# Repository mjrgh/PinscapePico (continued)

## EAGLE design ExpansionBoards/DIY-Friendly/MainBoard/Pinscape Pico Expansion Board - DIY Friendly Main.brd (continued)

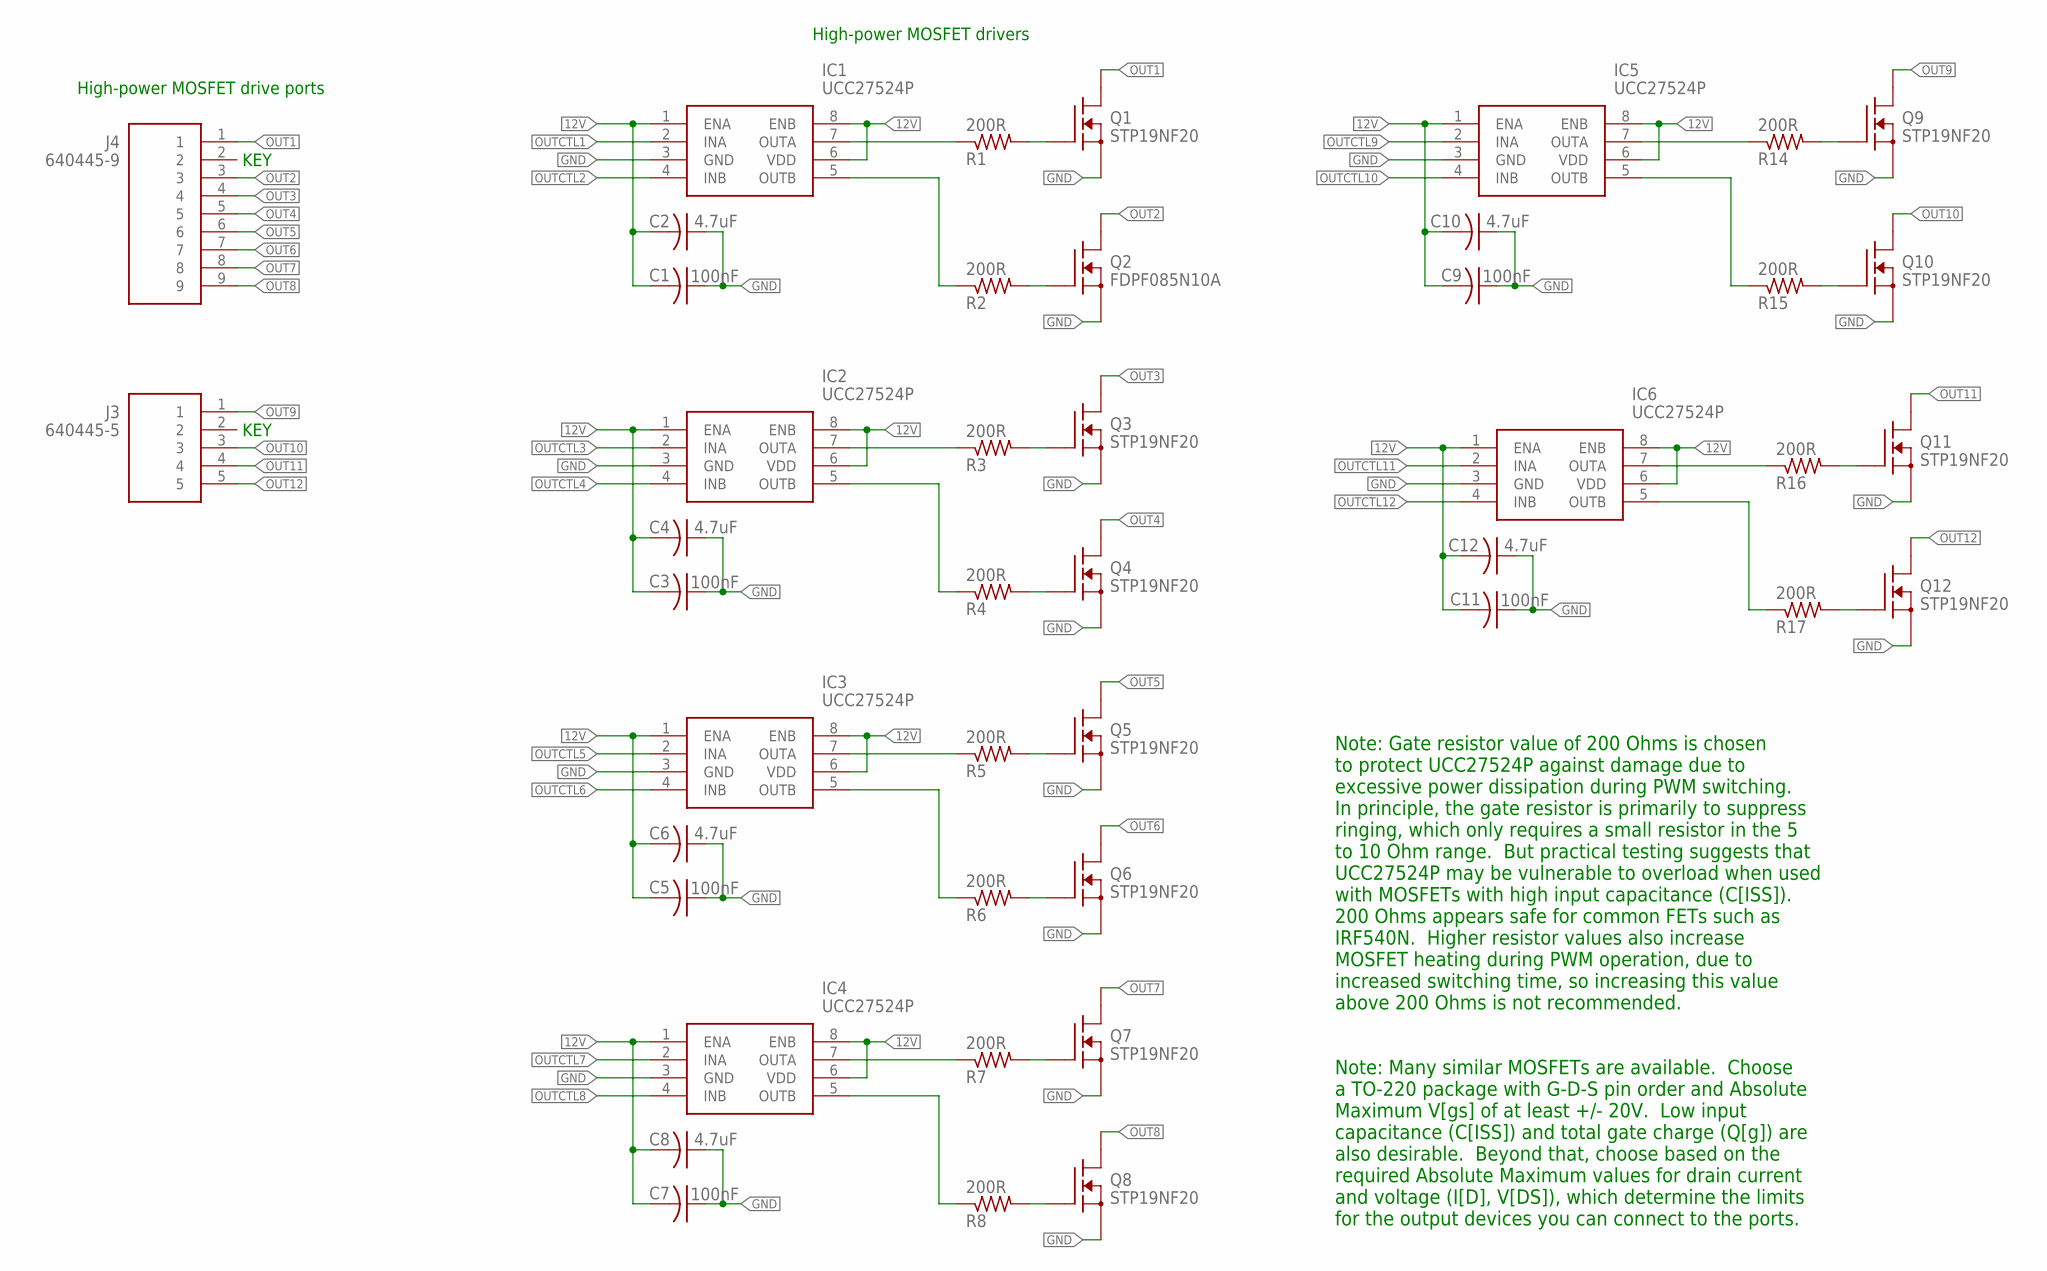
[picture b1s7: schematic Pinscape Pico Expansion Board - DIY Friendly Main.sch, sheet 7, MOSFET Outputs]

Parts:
C1, C3, C5, C7, C9, C11: 100nF; C025-024X044; PARTNO K104K15X7RF5TL2
C2, C4, C6, C8, C10, C12: 4.7uF; C025-024X044; PARTNO 810-FG14X5R1H475KRT0
IC1, IC2, IC3, IC4, IC5, IC6: UCC27524P; DIP794W53P254L959H508Q8N
J3: 640445-5; HDRV5W117P0X396_1X5_1981X762X1
J4: 640445-9; SHDR9W117P0X396_1X9_3566X762X1
Q1, Q3, Q4, Q5, Q6, Q7, Q8, Q9, Q10, Q11, Q12: STP19NF20; TO220BV; PARTNO FDPF085N10A
Q2: FDPF085N10A; TO220BV; PARTNO FDPF085N10A
R1, R2, R3, R4, R5, R6, R7, R8, R14, R15, R16, R17: 200R; 0204/5; PARTNO 660-MFS1/4DCT52R47R0

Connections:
12V: C1.2, C2.2, C3.2, C4.2, C5.2, C6.2, C7.2, C8.2, C9.2, C10.2, C11.2, C12.2, IC1.1 (ENA), IC1.6 (VDD), IC1.8 (ENB), IC2.1 (ENA), IC2.6 (VDD), IC2.8 (ENB), IC3.1 (ENA), IC3.6 (VDD), IC3.8 (ENB), IC4.1 (ENA), IC4.6 (VDD), IC4.8 (ENB), IC5.1 (ENA), IC5.6 (VDD), IC5.8 (ENB), IC6.1 (ENA), IC6.6 (VDD), IC6.8 (ENB); also elsewhere on the board
GND: C1.1, C2.1, C3.1, C4.1, C5.1, C6.1, C7.1, C8.1, C9.1, C10.1, C11.1, C12.1, IC1.3 (GND), IC2.3 (GND), IC3.3 (GND), IC4.3 (GND), IC5.3 (GND), IC6.3 (GND), Q1.3 (S), Q2.3 (S), Q3.3 (S), Q4.3 (S), Q5.3 (S), Q6.3 (S), Q7.3 (S), Q8.3 (S), Q9.3 (S), Q10.3 (S), Q11.3 (S), Q12.3 (S); also elsewhere on the board
unnamed: IC1.7 (OUTA), R1.1
unnamed: IC1.5 (OUTB), R2.1
unnamed: Q1.1 (G), R1.2
unnamed: Q2.1 (G), R2.2
unnamed: IC2.7 (OUTA), R3.1
unnamed: IC2.5 (OUTB), R4.1
unnamed: Q3.1 (G), R3.2
unnamed: Q4.1 (G), R4.2
unnamed: IC3.7 (OUTA), R5.1
unnamed: IC3.5 (OUTB), R6.1
unnamed: Q5.1 (G), R5.2
unnamed: Q6.1 (G), R6.2
unnamed: IC4.7 (OUTA), R7.1
unnamed: IC4.5 (OUTB), R8.1
unnamed: Q7.1 (G), R7.2
unnamed: Q8.1 (G), R8.2
unnamed: IC5.7 (OUTA), R14.1
unnamed: IC5.5 (OUTB), R15.1
unnamed: Q9.1 (G), R14.2
unnamed: Q10.1 (G), R15.2
unnamed: IC6.7 (OUTA), R16.1
unnamed: IC6.5 (OUTB), R17.1
unnamed: Q11.1 (G), R16.2
unnamed: Q12.1 (G), R17.2
OUT1: J4.1, Q1.2 (D)
OUT2: J4.3, Q2.2 (D)
OUT3: J4.4, Q3.2 (D)
OUT4: J4.5, Q4.2 (D)
OUT5: J4.6, Q5.2 (D)
OUT6: J4.7, Q6.2 (D)
OUT7: J4.8, Q7.2 (D)
OUT8: J4.9, Q8.2 (D)
OUT9: J3.1, Q9.2 (D)
OUT10: J3.3, Q10.2 (D)
OUT11: J3.4, Q11.2 (D)
OUT12: J3.5, Q12.2 (D)
OUTCTL1: IC1.2 (INA); also elsewhere on the board
OUTCTL2: IC1.4 (INB); also elsewhere on the board
OUTCTL3: IC2.2 (INA); also elsewhere on the board
OUTCTL4: IC2.4 (INB); also elsewhere on the board
OUTCTL5: IC3.2 (INA); also elsewhere on the board
OUTCTL6: IC3.4 (INB); also elsewhere on the board
OUTCTL7: IC4.2 (INA); also elsewhere on the board
OUTCTL8: IC4.4 (INB); also elsewhere on the board
OUTCTL9: IC5.2 (INA); also elsewhere on the board
OUTCTL10: IC5.4 (INB); also elsewhere on the board
OUTCTL11: IC6.2 (INA); also elsewhere on the board
OUTCTL12: IC6.4 (INB); also elsewhere on the board

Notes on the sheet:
High-power MOSFET drive ports
KEY
High-power MOSFET drivers
Note: Gate resistor value of 200 Ohms is chosen to protect UCC27524P against damage due to excessive power dissipation during PWM switching. In principle, the gate resistor is primarily to suppress ringing, which only requires a small resistor in the 5 to 10 Ohm range. But practical testing suggest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
Note: Many similar MOSFETs are available. Choose a TO-220 package with G-D-S pin order and Absolute Maximum V[gs] of at least +/- 20V. Low input capacitance (C[ISS]) and total gate charge (Q[g]) are also desirable. Beyond that, choose based on the required Absolute Maximum values for drain current 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

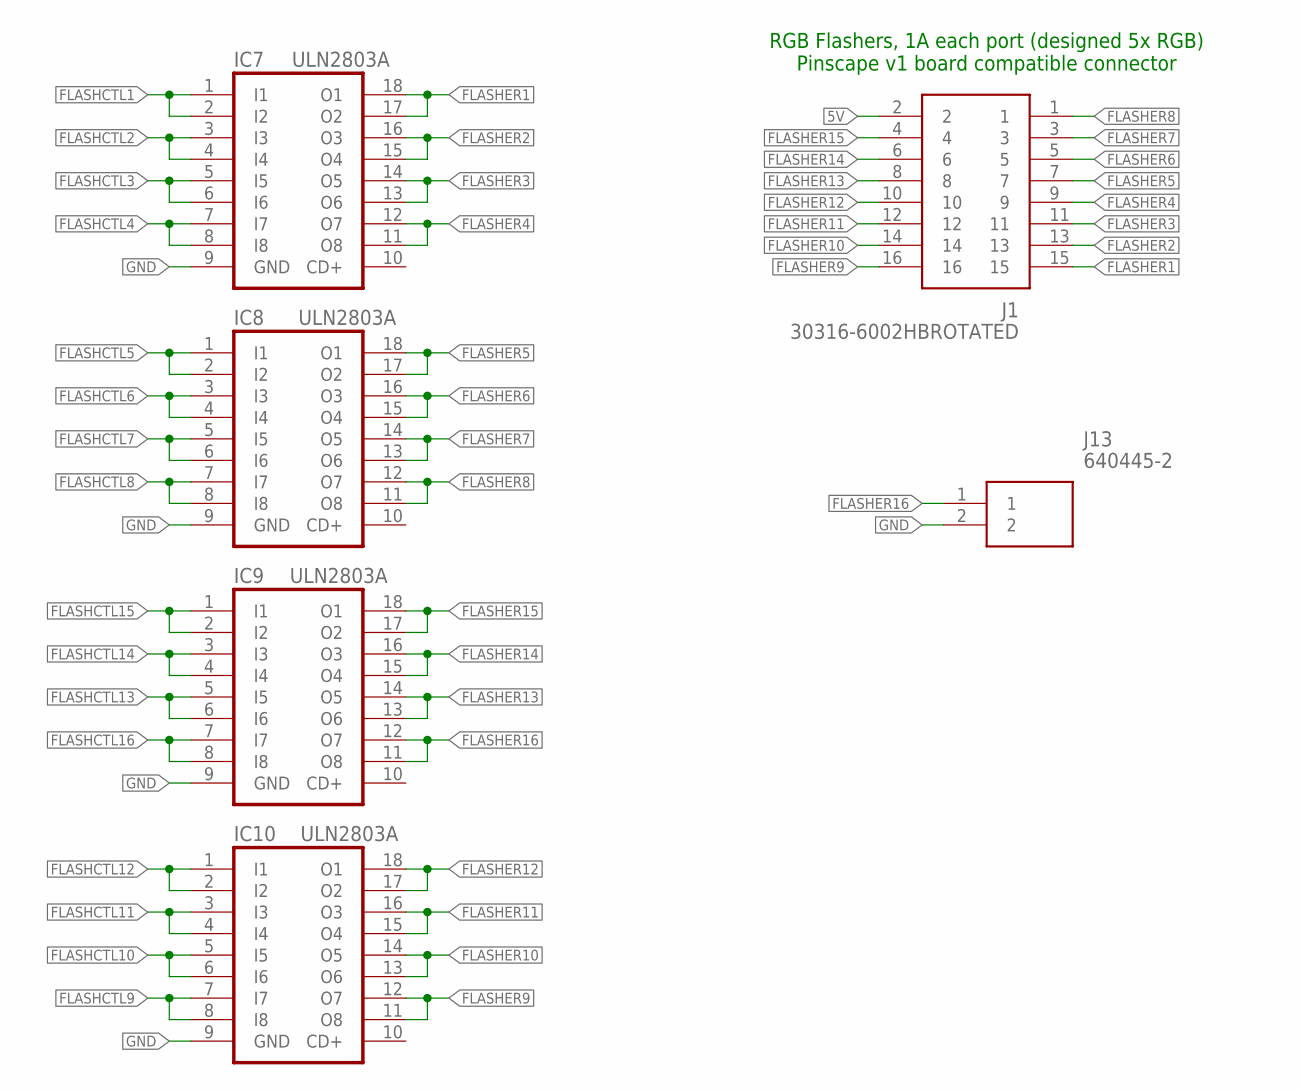
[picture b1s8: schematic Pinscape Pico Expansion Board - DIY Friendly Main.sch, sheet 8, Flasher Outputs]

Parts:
IC7, IC8, IC9, IC10: ULN2803A; DIL18
J1: 30316-6002HBROTATED; 3M-30316-6002HB-ROTATED
J13: 640445-2; SHDR2W117P0X396_1X2_792X762X11

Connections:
5V: J1.2; also elsewhere on the board
FLASHCTL1: IC7.1 (I1), IC7.2 (I2); also elsewhere on the board
FLASHCTL2: IC7.3 (I3), IC7.4 (I4); also elsewhere on the board
FLASHCTL3: IC7.5 (I5), IC7.6 (I6); also elsewhere on the board
FLASHCTL4: IC7.7 (I7), IC7.8 (I8); also elsewhere on the board
FLASHCTL5: IC8.1 (I1), IC8.2 (I2); also elsewhere on the board
FLASHCTL6: IC8.3 (I3), IC8.4 (I4); also elsewhere on the board
FLASHCTL7: IC8.5 (I5), IC8.6 (I6); also elsewhere on the board
FLASHCTL8: IC8.7 (I7), IC8.8 (I8); also elsewhere on the board
FLASHCTL9: IC10.7 (I7), IC10.8 (I8); also elsewhere on the board
FLASHCTL10: IC10.5 (I5), IC10.6 (I6); also elsewhere on the board
FLASHCTL11: IC10.3 (I3), IC10.4 (I4); also elsewhere on the board
FLASHCTL12: IC10.1 (I1), IC10.2 (I2); also elsewhere on the board
FLASHCTL13: IC9.5 (I5), IC9.6 (I6); also elsewhere on the board
FLASHCTL14: IC9.3 (I3), IC9.4 (I4); also elsewhere on the board
FLASHCTL15: IC9.1 (I1), IC9.2 (I2); also elsewhere on the board
FLASHCTL16: IC9.7 (I7), IC9.8 (I8); also elsewhere on the board
FLASHER1: IC7.17 (O2), IC7.18 (O1), J1.15
FLASHER2: IC7.15 (O4), IC7.16 (O3), J1.13
FLASHER3: IC7.13 (O6), IC7.14 (O5), J1.11
FLASHER4: IC7.11 (O8), IC7.12 (O7), J1.9
FLASHER5: IC8.17 (O2), IC8.18 (O1), J1.7
FLASHER6: IC8.15 (O4), IC8.16 (O3), J1.5
FLASHER7: IC8.13 (O6), IC8.14 (O5), J1.3
FLASHER8: IC8.11 (O8), IC8.12 (O7), J1.1
FLASHER9: IC10.11 (O8), IC10.12 (O7), J1.16
FLASHER10: IC10.13 (O6), IC10.14 (O5), J1.14
FLASHER11: IC10.15 (O4), IC10.16 (O3), J1.12
FLASHER12: IC10.17 (O2), IC10.18 (O1), J1.10
FLASHER13: IC9.13 (O6), IC9.14 (O5), J1.8
FLASHER14: IC9.15 (O4), IC9.16 (O3), J1.6
FLASHER15: IC9.17 (O2), IC9.18 (O1), J1.4
FLASHER16: IC9.11 (O8), IC9.12 (O7), J13.1
GND: IC7.9 (GND), IC8.9 (GND), IC9.9 (GND), IC10.9 (GND), J13.2; also elsewhere on the board

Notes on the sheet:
RGB Flashers, 1A each port (designed 5x RGB) Pinscape v1 board compatible connector

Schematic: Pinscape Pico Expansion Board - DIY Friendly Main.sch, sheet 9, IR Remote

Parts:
C14: 4.7uF; C025-024X044; PARTNO 810-FG14X5R1H475KRT0
D3, D4: 1N4148; DO35-7
J10: 215079-4; 2150794
J11: 640454-2; HDRV2W66P0X254_1X2_762X572X100
Q13: BC337-25; BC33725
R19: 540R; 0204/7; PARTNO 660-MFS1/4DCT52R47R0
R31: 2R5; 0204/7; PARTNO 660-MFS1/4DCT52R47R0

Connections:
3V3_PICO: J10.1; also elsewhere on the board
5V: C14.1, J11.1; also elsewhere on the board
$N377: D3.A, Q13.2 (B), R19.2
GND: C14.2, D4.C, J10.2, J10.4, R31.1; also elsewhere on the board
IR_IN: J10.3; also elsewhere on the board
IR_LED_CATHODE: J11.2, Q13.1 (C)
IR_OUT: R19.1; also elsewhere on the board
unnamed: D3.C, D4.A
unnamed: Q13.3 (E), R31.2

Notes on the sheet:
IR REMOTE CONTROL TRANSMITTER Use with VSLB4940, TSAL6400, or a similar IR LED with a peak wavelength around 940nm. Set the current-sense resistor according to the desired forward current on the IR LED. Set to 200 mA for VSLB4940 or TSAL6400; for others, use a current between the "continuous" and "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
IR REMOTE RECEIVER CONNECTOR This header allows connecting an IR receiver (TSOP38438) on a separate circuit board, connected to the main board with a 4-conductor ribbon cable. The board should include the VCC supply filter circuit (220R + 150nF) shown in the data sheet.
===> IRED Cathode (-)
===> IRED Anode (+)
Note: TE Connectivity Micro-Match 215079-4 base pairs with 215083-4 on-cable IDC connector.
CURRENT-SENSE RESISTOR Resistor sets current to I(LED) = 0.5V/R R=2.5 ohms -> 200mA current
NPN substitutes: choose any medium-power NPN with Hfe around 100
IR EMITTER / IR RECEIVER The emitter and receiver are designed to be installed remotely to allow placing them in suitable line-of-sight locations.

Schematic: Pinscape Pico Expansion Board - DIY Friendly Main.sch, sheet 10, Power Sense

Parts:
C13: 100nF; C025-024X044; PARTNO K104K15X7RF5TL2
IC11: SN74HC74NE4; DIP794W53P254L1930H508Q14N
IC12: S-80833CLY; TO-92_(TO-226)
IC13: PC827; DIL08
R18: 240R; 0204/7; PARTNO 660-MFS1/4DCT52R47R0
R20, R22: 10K; 0204/7; PARTNO mfr-12frrf52-10k
R21: 360R; 0204/7; PARTNO 660-MFS1/4DCT52R47R0

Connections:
3V3_PICO: IC13.6 (COL); also elsewhere on the board
5V: C13.1, IC11.2 (1D), IC11.4 (1!PRE), IC11.14 (VCC), IC12.2 (VDD), IC13.8 (COL); also elsewhere on the board
GND: C13.2, IC11.7 (GND), IC12.3 (GND), R18.1, R20.2, R21.1, R22.1; also elsewhere on the board
unnamed: IC11.3 (1CLK), IC13.7 (EMIT), R20.1
unnamed: IC13.2 (C), R18.2
unnamed: IC11.1 (!1CLR), IC12.1 (OUT)
unnamed: IC13.4 (C), R21.2
unnamed: IC11.5 (1Q), IC13.3 (A)
PSU2_STATUS_SENSE: IC13.5 (EMIT), R22.2; also elsewhere on the board
PSU2_STATUS_SET: IC13.1 (A); also elsewhere on the board

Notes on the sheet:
PSU2 Power Sensing This circuit monitors the status of a secondary power supply (PSU2) that's hard-switched on and off with the overall pinball cabinet power. The status circuit maintains its own memory of the power state, independently of the Pico's power state, which satisfies two important condi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
POR part selection: The POR is triggered by the voltage on the 5V supply crossing a threshold voltage, so we must choose a POR whose threshold voltage slightly below the MINIMUM voltage that the 5V supply maintains when powered on and operating stably. Nominally, this would be 4.75V for an ATX supp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
Note: RESET signal must be ACTIVE LOW

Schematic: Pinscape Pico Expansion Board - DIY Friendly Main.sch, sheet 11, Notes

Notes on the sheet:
I2C Address Map (7-bit notation) $18 LIS3DH (Accelerometer) $30 Pico PWM Helper (main board) $31 Pico PWM Helper #1 (power board) $32 Pico PWM Helper #2 (power board) $48 ADS1115 (ADC) $68 DS1307 (RTC clock/calendar chip) [On Power board]
Copyright and License Info Pinscape Pico DIY Friendly Expansion Board Copyright 2024, 2025 Michael J Roberts BSD 3-clause license

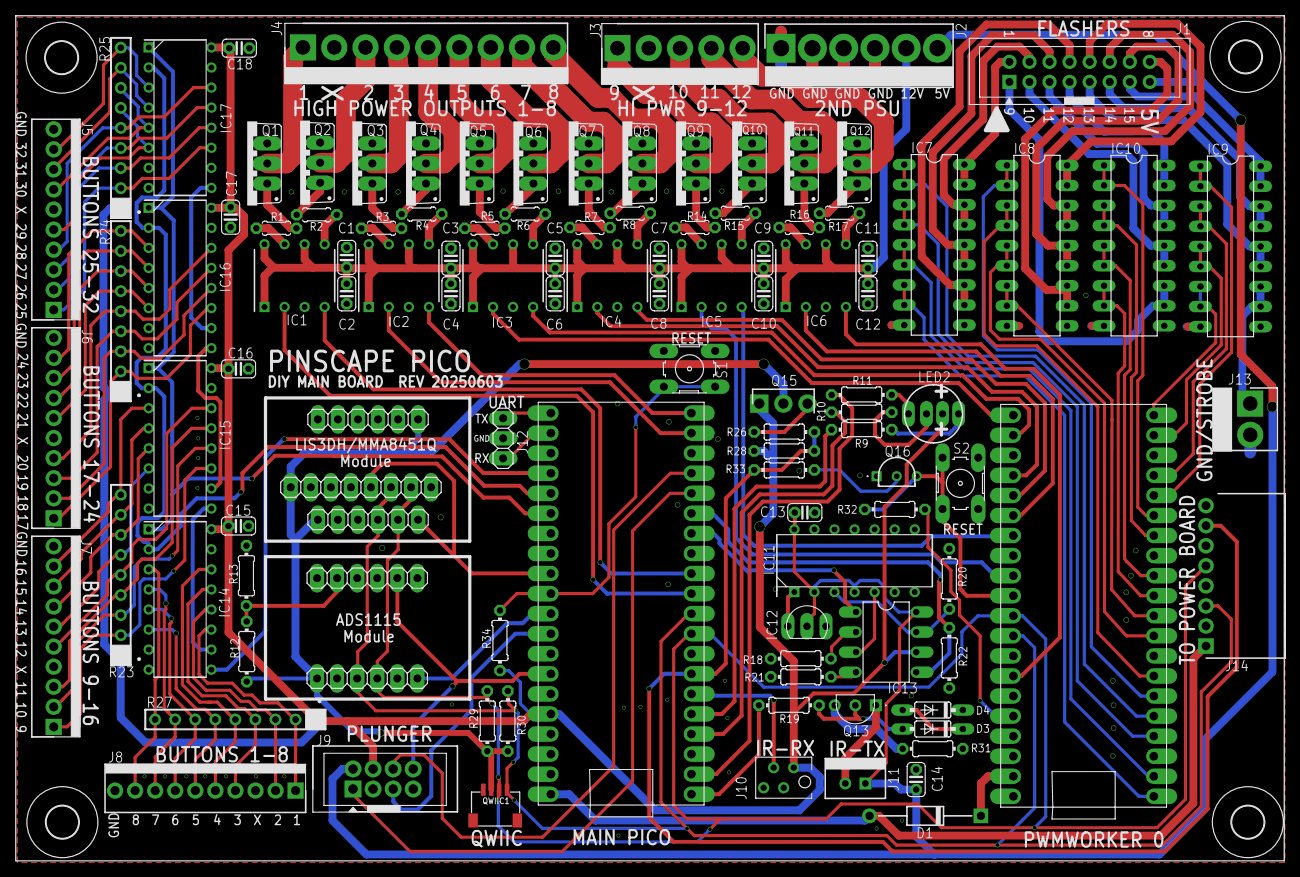
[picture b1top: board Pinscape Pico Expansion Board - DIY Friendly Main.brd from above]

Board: 2 copper layers, 160.6 x 107.0 mm, 116 parts (0 on the bottom side), 161 nets.

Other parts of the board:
U$1, U$2, U$3, U$4: 4,1

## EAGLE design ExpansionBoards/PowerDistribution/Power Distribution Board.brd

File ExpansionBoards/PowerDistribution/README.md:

# Pinscape Pico Power Distribution Board

This is a prototype design for a power distribution board for virtual
pinball cabinets.  It's nominally designed to be used with the
Pinscape Pico expansion boards, but it could really be used with just
about any pin cab setup, with or without an I/O board like Pinscape.

## 120VAC vs 220/230/240VAC

I use the term "120VAC" here to refer to the line voltage - the
voltage from your wall outlet plug.  I call it "120VAC" just to make
it concrete and avoid jargon, but it makes it sound like you can
*only* use the board with 120VAC plugs, which isn't true.  What I
really mean is **line voltage**, whatever that happens to be in your
region.

To be clear, the board will also work in countries with 220VAC to
240VAC outlets, which is the standard in Europe and many other parts
of the world.

The board really doesn't care what the line voltage is, because it
doesn't have any transformers or other parts designed around specific
voltages.  It just routes the line voltage to the various headers.
That lets you use any voltage, as long as it's within the upper limits
for all of the parts.  The limiting factor is the switching relay,
which is rated for up to 240VAC.

## Danger - high voltage

This board provides connections to the 120VAC (or 240VAC) wall outlet
power inputs to the various DC power supplies.  It also has a section
for 48VDC power.  Line voltage and 48VDC are both hazardous, capable
of causing electric shock and fires.  The board must be installed in
the cabinet so that it's shielded from accidental contact with the
operator or contact with loose articles.  It should have either a
grounded metal enclosure (grounded to Earth ground through the AC
outlet) or an insulated enclosure.  Always unplug it from all outside
power sources when doing any work on the board.

## Features

This board has several functions special to pin cabs:

* "Smart" power switching: Virtual pin cabs typically have two or
more DC power supplies: the ATX power supply that runs the main PC,
and one or more auxiliary supplies for running feedback devices
(lights, motors, solenoids, etc).  There are often several auxiliary
supplies to meet the varying voltage requirements for the feedback
devices, such as a 24V supply for contactors and solenoids, a 48V
supply for pinball coils, and a 5V/12V dual supply for LEDs, motors,
and smaller solenoids.  Most people like to use a single "soft power"
button to control power to the PC, and would like all of the auxiliary
devices to switch on and off automatically with the PC.  This board
takes care of that for the auxiliary power supplies, by providing a
relay that switches the 120VAC mains power to all of the secondary
supplies according to the 12V rail from the main PC power supply.
Just plug an unused floppy-disk power connector from your PC ATX
power supply into the matching port on this board, and it'll control
the relay, which in turn switches AC power to your auxiliary power
supplies.

* A switched 120VAC output port is also provided, for connecting to
a plain power strip as its AC power input, turning the plain power
strip into a smart switched power strip that turns on and off
according to the main PC power status.  You can use this to control
power to other equipment in the pin cab, such as TVs/monitors and
audio amplifiers, so that everything turns on and off automatically
according to the main PC power status.  This eliminates the need to
buy a separate "smart power strip" for other equipment.

* DC power supply wire routing: Most of the switch-mode power supplies
(SMPS) that people use in pin cab projects have exposed screw
terminals for all of their wiring, including the 120VAC power input.
The power distribution board has a corresponding shrouded header for
each power supply ("shrouded" means that the pins are enclosed in a
plastic housing to protect against accidental contact).  This lets you
create a single pluggable cable for each SMPS, so that you don't have
to mess with the screw terminals as often - just wire the screw
terminal once, and then you can safely plug and unplug it via the
power distribution board connector.  This is simpler when doing
maintenance work, reduces the chances of errors when reconnecting
wires, and makes the wiring a little neater.  The 120VAC power
connectors to these headers use the switched "smart" power lines, so
all of your SMPS units wired through these connectors will
automatically power on and off according to the main PC power status.

* Filtering: This board includes some large capacitors to help filter
voltage spikes on the high-voltage 48V supply, to help provide rapid
delivery to high-current devices like solenoids.  This should also
help reduce electrical interference from those devices.

* Coin-door interlock: The board includes a coin-door interlock
circuit for the 48VDC supply, so that power on the 48VDC rail is cut
off when the coin door is open.  This is a protective measure that
real pinball machines started including in the 1990s to protect
operators from accidentally touching a live high-voltage wire while
they have the machine opened up for servicing, and it's a good feature
to include in a virtual pin cab for the same reason.  The wiring to
the coin door switch itself is a low-voltage (5V) logic circuit, for
added safety.

* 6.3V lamp supply: The board includes a regulator that provides a
6.3VDC supply for #555 lamps, which are the lamps found in
arcade-style pushbuttons.  Those pinball bulbs *can* run on 5V, but
they'll look at bit dim at 5V, so it's nice to have a 6.3 supply.  But
it's hard to find a 6.3V SMPS, so this board provides its own 6.3V
output via a voltage regulator sourced from the 12V supply.  The
regulator can supply up to 5 Amps on the 6.3V output, which is enough
for about 20 incandescent #555 bulbs, or over 100 LED equivalents.

* OEM power supply ports: The board has ports designed to connect
to the screw terminals on typical 5V/12VDC, 24VDC, and 48VDC OEM
power supplies of the sort you can find on Amazon and eBay.  These
supplies almost all come with a set of screw terminals for 120VAC
line/neutral/ground inputs, and +/- DC outputs.  The power distribution
board has matching terminals for each type of power supply, so that
you can easily wire each supply to the distro board, keeping the
wiring tidy.  The 120VAC connections to the OEM supplies are all
switched through the "smart" relay, so that all power supplies
automatically switch on and off with the main PC.

* Secondary PC ATX power supply port: A standard 24-pin motherboard
connector is provided for a secondary PC ATX power supply, which can
be used **instead of** a standalone 5V/12V OEM power supply.  Many pin
cab builders use PC ATX power supplies as their 5V/12V supplies simply
because they're so widely available, and they're often cheaper than
standalone SMPS units with similar amperage capacity.  This board
makes it extremely easy to use a PC ATX supply, since it has a
standard motherboard connector, **and** it automatically controls the
"soft" power to the supply through the smart power switching feature.
Plug your secondary ATX power supply's AC cord directly into a regular
outlet, and plug the main 24-pin connector into the power distribution
board's mating 24-pin header.  The smart power switching will then
automatically turn the secondary power supply on and off according to
the main PC power supply status.

* Power hub: The board includes an ample set of output ports for 5V,
6.3V, 12V, 24V, 48V, and GND connections, for running wiring to the
various feeedback devices.  This is a convenience to help tidy up your
wiring by providing enough ports that you won't have to improvise by
tying multiple wires together.

* Indicator LEDs: all of the output DC power rails have indicator LEDs
that light when power to that voltage level is on.  This is helpful
for safety (since you can tell at a glance that power is on) as well
as for troubleshooting.

## Operation Mode Options

When you build the board, you can select one of two operational modes:

* Smart power switching, based on the main PC 5V power supply status

* Always-On mode

### Smart power switching

In this mode, the 120V power sent to all of the power supplies is
switched based on the status of the 5V power rail from the main PC,
via the MAIN PC POWER header connection.  This lets the main PC control
power to all of the secondary power supplies, so that all of the other
devices automatically power on and off along with the main PC.

You MUST plug a floppy disk power connector from your main PC into the
MAIN PC POWER header when operating in this mode, so that the board
can tell when the main PC is powered on.

<b>DO NOT</b> install anything in the slots marked **W1** and **W2**.
Those are only used in ALWAYS-ON mode.

### Always-On

If ALWAYS-ON mode is selected when you build the board, all of the power
supplies are connected to 120VAC mains power ALWAYS.  There is no "smart"
switching based on the main PC power supply status.  Use this mode if
you **already** have your own smart power switching mechanism, such as
a smart power strip that controls its outlets based on whether the main
PC is on or off.  You can also use ALWAYS-ON mode if you use a hard On/Off
switch to controls the main 120V power to the entire system.

To build the board in ALWAYS-ON mode, **DO NOT POPULATE** the following parts:

* K1 (Relay)
* OK1 (Optocoupler)
* R4 (resistor)

Instead, **install jumper wires** at the slots marked **W1** and **W2**.
(A jumper wire is simply a short piece of wire inserted into the pads
as marked - effectively a zero-ohm resistor.)

In this mode, there's no need to plug anything into the MAIN PC POWER header.

## Connectors

This board uses three connector types:

* <b>Molex MicroFit+: </b> These are used for most of the wiring to
the external power supplies.  I chose these because they can handle
high currents, the pins are all enclosed in plastic (which protects
against accidental short circuits if you drop a screwdriver or
anything like that), and each connector is designed so that you can't
plug in the wrong cable, and you can't plug in the right cable in the
wrong direction.  This makes maintenance work easier, since you don't
have to remember which cable goes where - each cable only fits in one
header.
 
  These connectors use crimp-pin housings, which makes them a little bit
  of work to assemble, so I only used them for the connections to the
  power supplies.

* <b>TE Connectivity MTA-156:</b> These are used for the power
distribution side, to carry power and ground to your devices and other
circuit boards.  These are large connectors designed for high
currents, and they have "ramps" that prevent plugging in the connector
in the wrong direction.  I used different pin counts for each header
of this type, which should make it fairly obvious which plug goes with
which header.

  I chose these because the wire housings use IDC termination, which is
  faster and easier to assemble than the main alternative, crimp pins.
  The only thing to watch out for is that each housing type only works
  with one wire gauge, so you have to be sure to use the right wire type
  with each plug.

* <b>Mate-N-Lok:</b> This is the special connector that mates with the
standard floppy disk power connectors found on virtually all ATX power
supplies.  This is used for the connection to the primary PC power supply.
It makes it extremely easy to connect the PC power supply, since you just
need to plug in a free floppy disk connector.

* <b>Molex Mini-Fit Jr:</b> This is another PC-compatible connector,
in this case, the ATX 24-pin motherboard connector.  This is provided
in case you want to use an off-the-shelf ATX power supply as your 5V
and 12V source.  If so, you can just plug its motherboard power cable
directly into the 24-pin header on the power distribution board. (If
your power supply comes with a 20-pin connector, that's also
compatible with this header.)  You can omit this header if you're not
using an ATX supply for your 5V/12V source.

## Ground interconnects

This board connects all of the power supply grounds together, and
connects them all to the Earth ground from the 120VAC line power
input.  This is generally considered the safest configuration, because
it ensures that all voltages in the cabinet have the same 0V reference
point.

Note that all PC ATX power supplies connect the DC ground to the AC
Earth ground internally, since this is required by the ATX
specifications.  Power bricks and bare-metal-case power supply units
might or might not connect the grounds internally, but connecting them
to the board will interconnect the grounds whether or not they're
connected internally in the power supply units.

## Coin door interlock

The coin door interlock circuit cuts off power to the 48VDC output
pins whenever the two pins on the **COIN DOOR INTERLOCK** header are
not shorted together.  You should connect these two pins to the
NORMALLY OPEN and COMMON terminals (respectively) of your coin door
switch.  The switch should then be positioned behind the coin door so
that the coin door CLOSES the switch when the door is closed.  This is
the standard setup that real pinball machines have used for many
years, so it's easy to replicate in a virtual pin cab if you're using
standard parts.  See [Coin Door](http://mjrnet.org/pinscape/BuildGuideV2/BuildGuide.php?sid=coinDoor)
in the [Pinscape Build Guide](http://mjrnet.org/pinscape/BuildGuideV2/BuildGuide.php)
for the recommended parts and physical installation details.

If you're not using a 48V power supply, there's no need to connect
any of this.

If don't wish to use the interlock feature, you can simply create a
dummy connector for the COIN DOOR INTERLOCK header that shorts the two
pins together.  I don't recommend doing this, since it bypasses what I
consider an important safety feature, but it might be necessary if
your cabinet is constructed in such a way that there's no good way to
install a switch that detects when the cabinet is opened up for
service.  If you omit the safety interlock, you should always
completely power down your system manually before working inside the
cab.

Note that the coin door interlock **only** cuts power to the 48V rail.
It **doesn't** cut power to 5V, 6.3V, 12V, or 24V, or to the Pinscape
Pico boards.  This is because the interlock is designed primarily for **human**
safety, and the lower voltages are less likely to cause harm to a human.
However, be aware that ALL of the voltages are nonetheless quite hazardous
to the **equipment** in the pin cab, and all of them are quite capable
of starting fires.  Always completely power off the system if you're
going to be moving wires around or doing anything where you might
cause a short circuit.  It's all too easy to destroy expensive
equipment with a misplaced screwdriver when the power is hot.  People
are posting to the forums all the time about boards they destroyed
by accidentally touching a live 12V wire to the wrong terminal.

## Power capacity

The Molex Micro-Fit connectors used for the SMPS inputs are rated for
13A per pin, so this is the upper limit for each voltage level in the
system.  If you plan to use anywhere close to the 13A current limit,
use 18 AWG wire for the SMPS connections.

The different voltage supplies are all independent of one another, so
you can be using 13A at 12V and 13A at 24V at the same time without
overloading any of the connector pins.

If the power supplies you're using have lower individual current
limits, the lower limits will apply, again on an individual basis for
each voltage-level circuit.

The 13A limit on each voltage level should be adequate for most
virtual pinball cabinets.  The one likely exception is if you're using
very long LED light strips.  Those can draw 3A or more per meter, so
you'll reach the 13A limit at about 4 meters.  The best solution would
be to power those from a separate power supply connected directly to
the light strips, without going through the power distribution board.

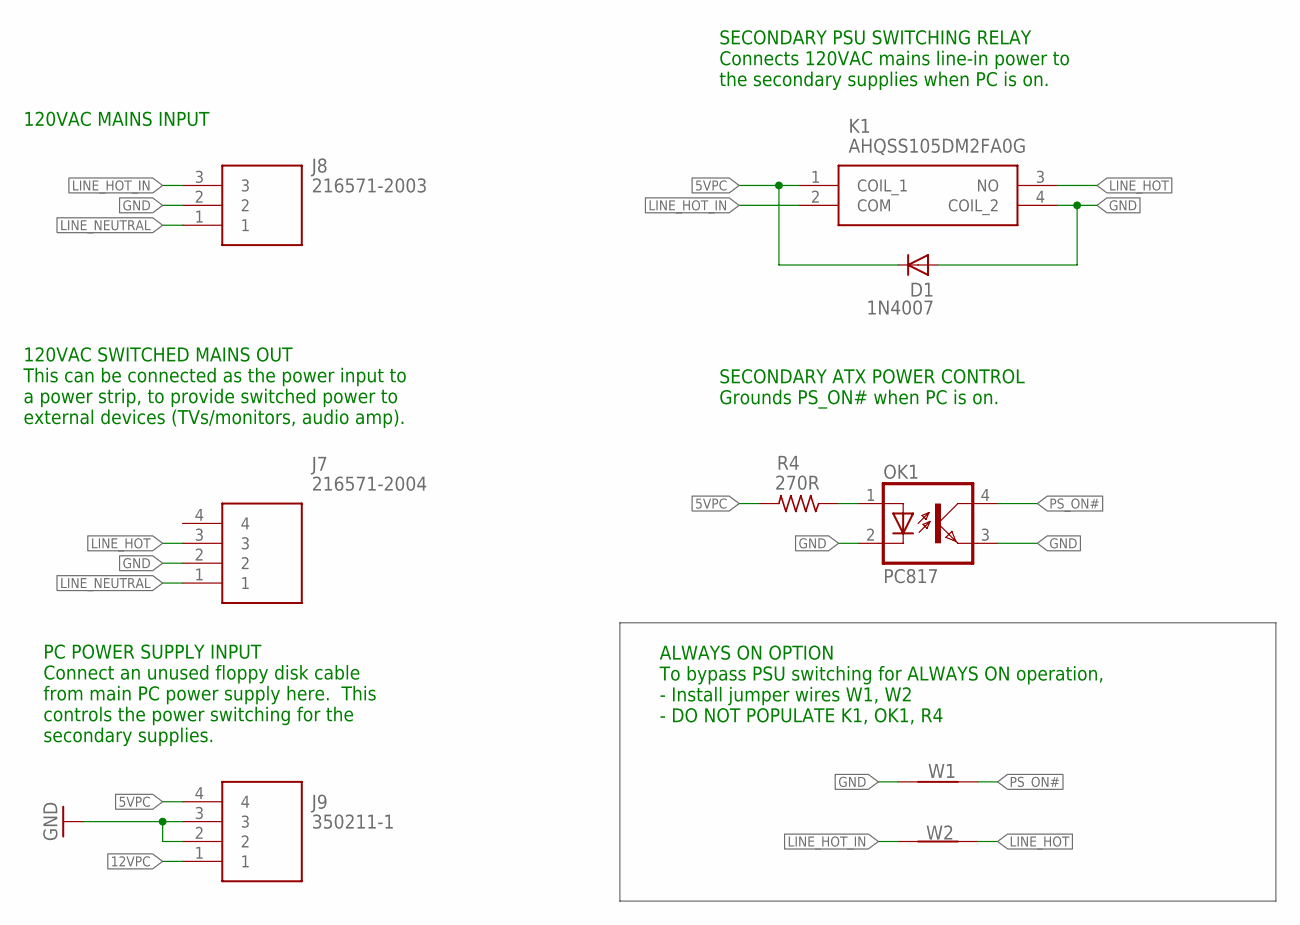
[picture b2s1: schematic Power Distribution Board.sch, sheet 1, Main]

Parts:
D1: 1N4007; DO41-10
J7: 216571-2004; 216571-YY04_1
J8: 216571-2003; 216571-YY03_1
J9: 350211-1; 3502111
K1: AHQSS105DM2FA0G
OK1: PC817; DIL04
R4: 270R; 0204/7
W1, W2: JUMPER-WIRE

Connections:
5VPC: D1.C, J9.4, K1.1 (COIL_1), R4.2
12VPC: J9.1
GND: D1.A, J7.2, J8.2, J9.2, J9.3, K1.4 (COIL_2), OK1.2 (C), OK1.3 (EMIT), W1.P$1; also elsewhere on the board
LINE_HOT: J7.3, K1.3 (NO), W2.P$2; also elsewhere on the board
LINE_HOT_IN: J8.3, K1.2 (COM), W2.P$1
LINE_NEUTRAL: J7.1, J8.1; also elsewhere on the board
unnamed: OK1.1 (A), R4.1
PS_ON#: OK1.4 (COL), W1.P$2; also elsewhere on the board

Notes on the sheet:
PC POWER SUPPLY INPUT Connect an unused floppy disk cable from main PC power supply here. This controls the power switching for the secondary supplies.
SECONDARY PSU SWITCHING RELAY Connects 120VAC mains line-in power to the secondary supplies when PC is on.
120VAC MAINS INPUT
SECONDARY ATX POWER CONTROL Grounds PS_ON# when PC is on.
120VAC SWITCHED MAINS OUT This can be connected as the power input to a power strip, to provide switched power to external devices (TVs/monitors, audio amp).
ALWAYS ON OPTION To bypass PSU switching for ALWAYS ON operation, - Install jumper wires W1, W2 - DO NOT POPULATE K1, OK1, R4

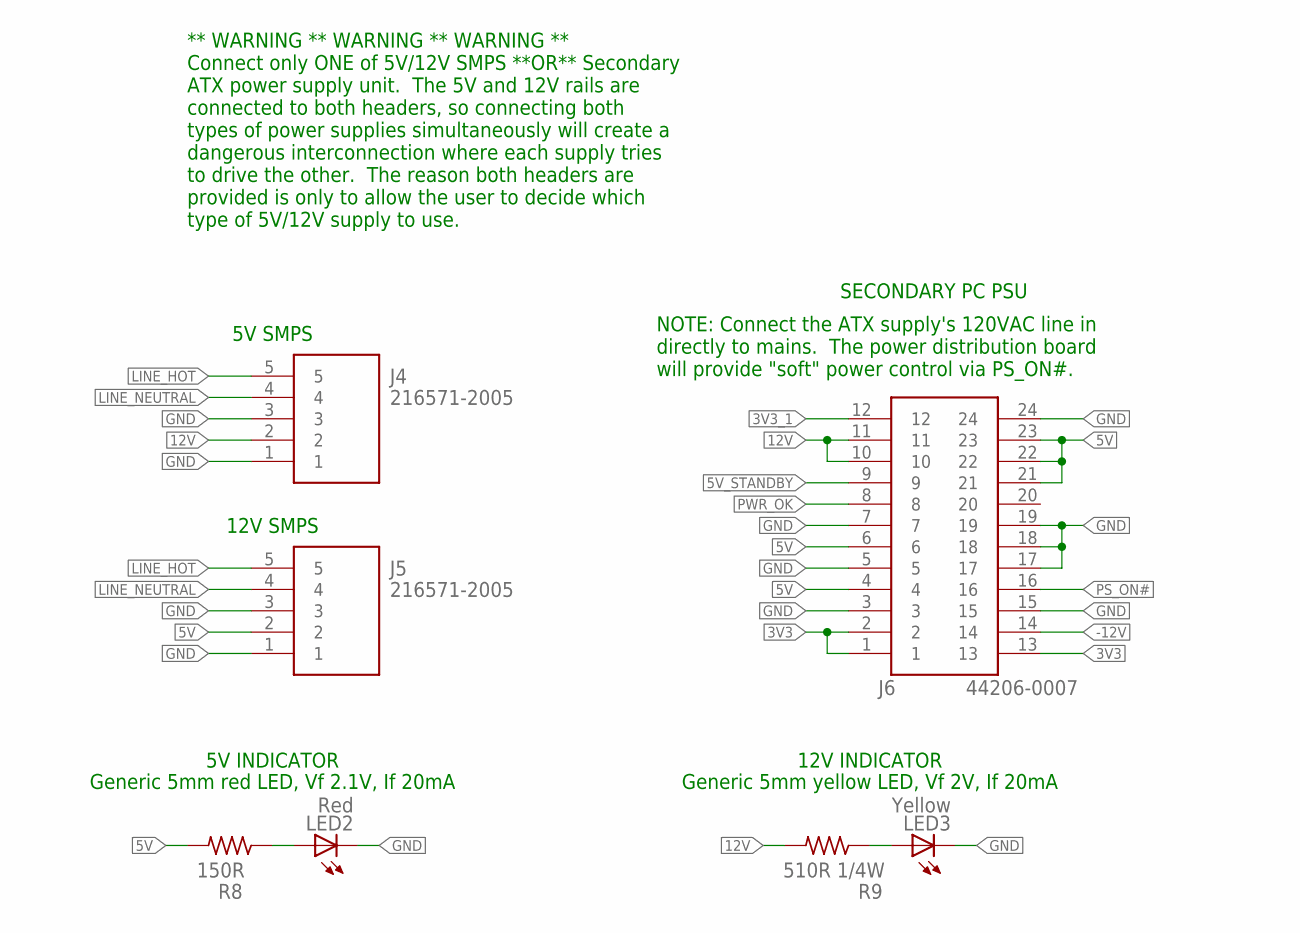
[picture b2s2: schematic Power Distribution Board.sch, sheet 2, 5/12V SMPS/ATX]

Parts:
J4, J5: 216571-2005; 216571-YY05_1
J6: 44206-0007; 44206-0007_1
LED2: Red; LED5MM
LED3: Yellow; LED5MM
R8: 150R; 0309/12
R9: 510R 1/4W; 0309/12

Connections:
3V3: J6.1, J6.2, J6.13
3V3_1: J6.12
5V: J5.2, J6.4, J6.6, J6.21, J6.22, J6.23, R8.2; also elsewhere on the board
5V_STANDBY: J6.9
12V: J4.2, J6.10, J6.11, R9.2; also elsewhere on the board
-12V: J6.14
GND: J4.1, J4.3, J5.1, J5.3, J6.3, J6.5, J6.7, J6.15, J6.17, J6.18, J6.19, J6.24, LED2.K (C), LED3.K (C); also elsewhere on the board
LINE_HOT: J4.5, J5.5; also elsewhere on the board
LINE_NEUTRAL: J4.4, J5.4; also elsewhere on the board
unnamed: LED2.A, R8.1
unnamed: LED3.A, R9.1
PS_ON#: J6.16; also elsewhere on the board
PWR_OK: J6.8

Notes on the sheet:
SECONDARY PC PSU
** WARNING ** WARNING ** WARNING ** Connect only ONE of 5V/12V SMPS **OR** Secondary ATX power supply unit. The 5V and 12V rails are connected to both headers, so connecting both types of power supplies simultaneously will create a dangerous interconnection where each supply tries to drive the othe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
NOTE: Connect the ATX supply's 120VAC line in directly to mains. The power distribution board will provide "soft" power control via PS_ON#.
5V INDICATOR
12V INDICATOR
Generic 5mm red LED, Vf 2.1V, If 20mA
Generic 5mm yellow LED, Vf 2V, If 20mA
5V SMPS
12V SMPS

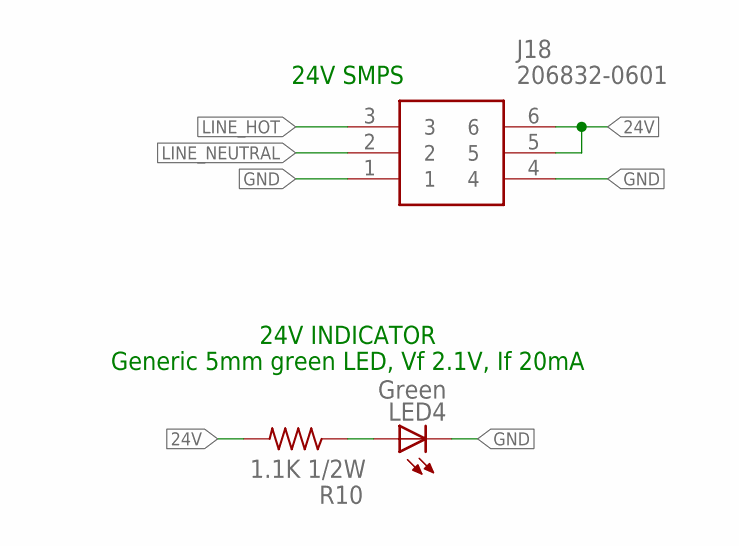
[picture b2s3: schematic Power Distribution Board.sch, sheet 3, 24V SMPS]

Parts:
J18: 206832-0601; 2068320601
LED4: Green; LED5MM
R10: 1.1K 1/2W; 0309/12

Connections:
24V: J18.5, J18.6, R10.2; also elsewhere on the board
GND: J18.1, J18.4, LED4.K (C); also elsewhere on the board
LINE_HOT: J18.3; also elsewhere on the board
LINE_NEUTRAL: J18.2; also elsewhere on the board
unnamed: LED4.A, R10.1

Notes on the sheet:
24V SMPS
24V INDICATOR
Generic 5mm green LED, Vf 2.1V, If 20mA

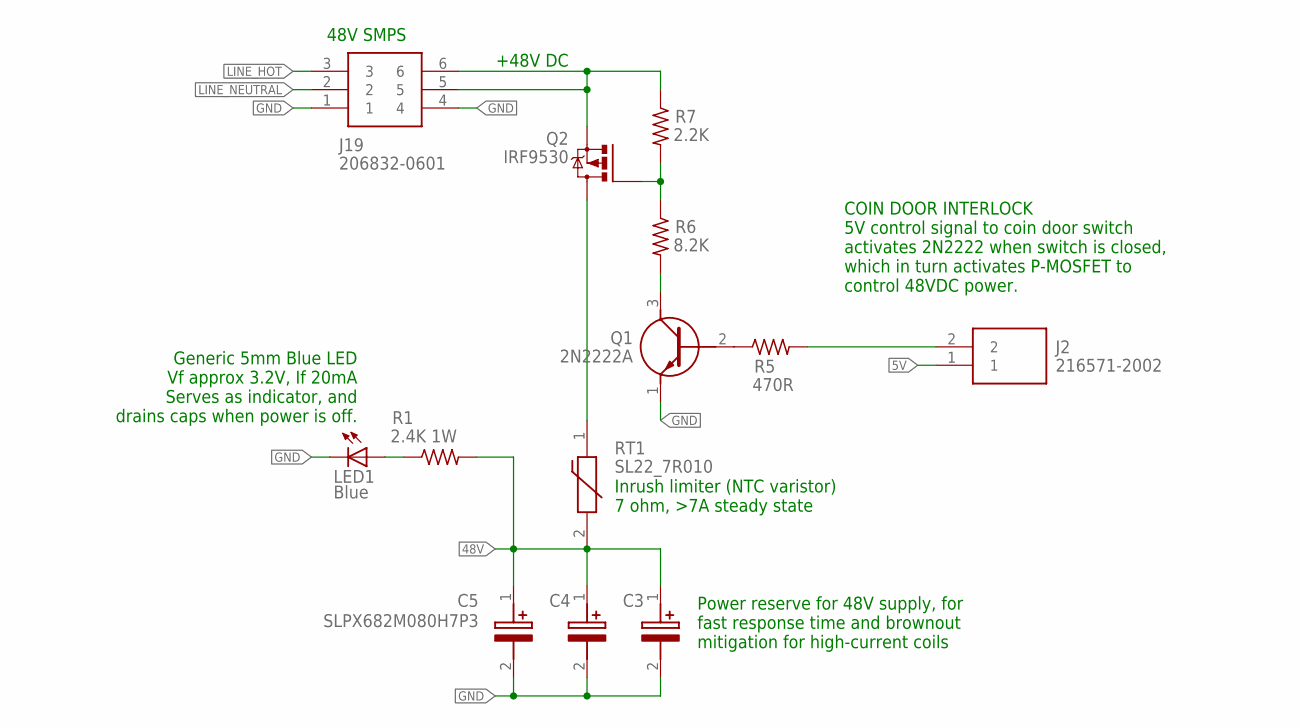
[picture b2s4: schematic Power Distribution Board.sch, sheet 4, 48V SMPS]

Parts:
C3, C4, C5: SLPX682M080H7P3; CAPPRD1000W100D3550H4200
J2: 216571-2002; 216571-YY02_1
J19: 206832-0601; 2068320601
LED1: Blue; LED5MM
Q1: 2N2222A
Q2: IRF9530; TO220BV
R1: 2.4K 1W; 0309/12
R5: 470R; 0204/7
R6: 8.2K; 0207/10
R7: 2.2K; 0207/10
RT1: SL22_7R010; SL227R010

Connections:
5V: J2.1; also elsewhere on the board
48V: C3.1 (+), C4.1 (+), C5.1 (+), R1.2, RT1.2; also elsewhere on the board
GND: C3.2 (-), C4.2 (-), C5.2 (-), J19.1, J19.4, LED1.K (C), Q1.1 (E); also elsewhere on the board
LINE_HOT: J19.3; also elsewhere on the board
LINE_NEUTRAL: J19.2; also elsewhere on the board
unnamed: J19.5, J19.6, Q2.S, R7.1
unnamed: Q2.D, RT1.1
unnamed: LED1.A, R1.1
unnamed: Q2.G, R6.1, R7.2
unnamed: Q1.3 (C), R6.2
unnamed: Q1.2 (B), R5.1
unnamed: J2.2, R5.2

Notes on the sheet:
48V SMPS
COIN DOOR INTERLOCK 5V control signal to coin door switch activates 2N2222 when switch is closed, which in turn activates P-MOSFET to control 48VDC power.
Power reserve for 48V supply, for fast response time and brownout mitigation for high-current coils
Inrush limiter (NTC varistor) 7 ohm, >7A steady state
Generic 5mm Blue LED Vf approx 3.2V, If 20mA Serves as indicator, and drains caps when power is off.
+48V DC

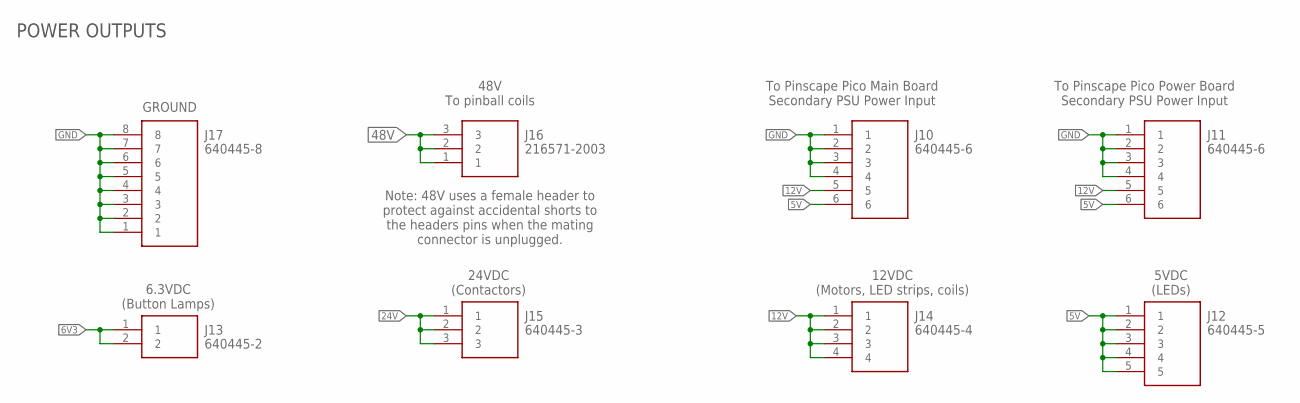
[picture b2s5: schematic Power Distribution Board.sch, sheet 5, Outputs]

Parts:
J10, J11: 640445-6; SHDR6W183P0X396_1X6_2377X762X1
J12: 640445-5; HDRV5W117P0X396_1X5_1981X762X1
J13: 640445-2; SHDR2W117P0X396_1X2_792X762X11
J14: 640445-4; SHDR4W117P0X396_1X4_1585X762X1
J15: 640445-3; HDRV3W140P0X396_1X3_1189X762X1
J16: 216571-2003; 216571-YY03_1
J17: 640445-8; SHDR8W117P0X396_1X8_3170X762X1

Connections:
5V: J10.6, J11.6, J12.1, J12.2, J12.3, J12.4, J12.5; also elsewhere on the board
6V3: J13.1, J13.2; also elsewhere on the board
12V: J10.5, J11.5, J14.1, J14.2, J14.3, J14.4; also elsewhere on the board
24V: J15.1, J15.2, J15.3; also elsewhere on the board
48V: J16.1, J16.2, J16.3; also elsewhere on the board
GND: J10.1, J10.2, J10.3, J10.4, J11.1, J11.2, J11.3, J11.4, J17.1, J17.2, J17.3, J17.4, J17.5, J17.6, J17.7, J17.8; also elsewhere on the board

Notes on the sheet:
GROUND
48V To pinball coils
POWER OUTPUTS
Note: 48V uses a female header to protect against accidental shorts to the headers pins when the mating connector is unplugged.
To Pinscape Pico Main Board Secondary PSU Power Input
6.3VDC (Button Lamps)
24VDC (Contactors)
12VDC (Motors, LED strips, coils)
5VDC (LEDs)
To Pinscape Pico Power Board Secondary PSU Power Input

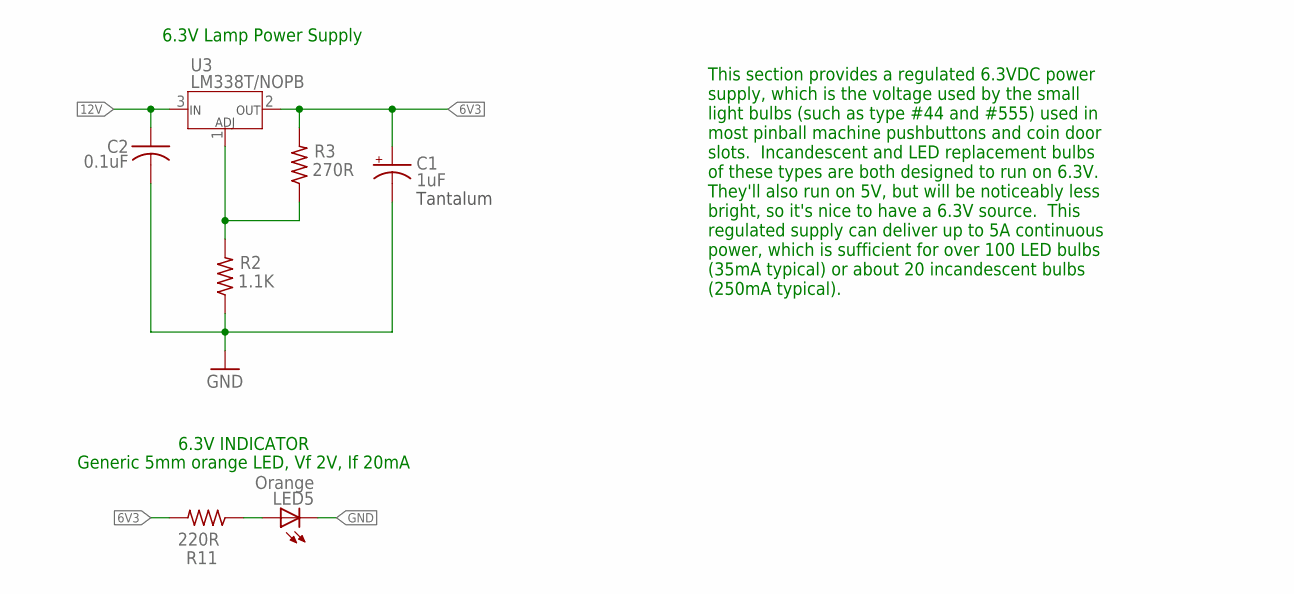
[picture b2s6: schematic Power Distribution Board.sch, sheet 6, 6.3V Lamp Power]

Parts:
C1: 1uF; B45181B
C2: 0.1uF; C025-030X050
LED5: Orange; LED5MM
R2: 1.1K; 0204/7
R3: 270R; 0204/7
R11: 220R; 0309/12
U3: LM338T/NOPB; T03B_TEX

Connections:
6V3: C1.+, R3.2, R11.2, U3.2 (OUT); also elsewhere on the board
12V: C2.1, U3.3 (IN); also elsewhere on the board
GND: C1.-, C2.2, LED5.K (C), R2.1; also elsewhere on the board
unnamed: LED5.A, R11.1
unnamed: R2.2, R3.1, U3.1 (ADJ)

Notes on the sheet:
6.3V Lamp Power Supply
This section provides a regulated 6.3VDC power supply, which is the voltage used by the small light bulbs (such as type #44 and #555) used in most pinball machine pushbuttons and coin door slots. Incandescent and LED replacement bulbs of these types are both designed to run on 6.3V. They'll also ru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
Tantalum
6.3V INDICATOR
Generic 5mm orange LED, Vf 2V, If 20mA
